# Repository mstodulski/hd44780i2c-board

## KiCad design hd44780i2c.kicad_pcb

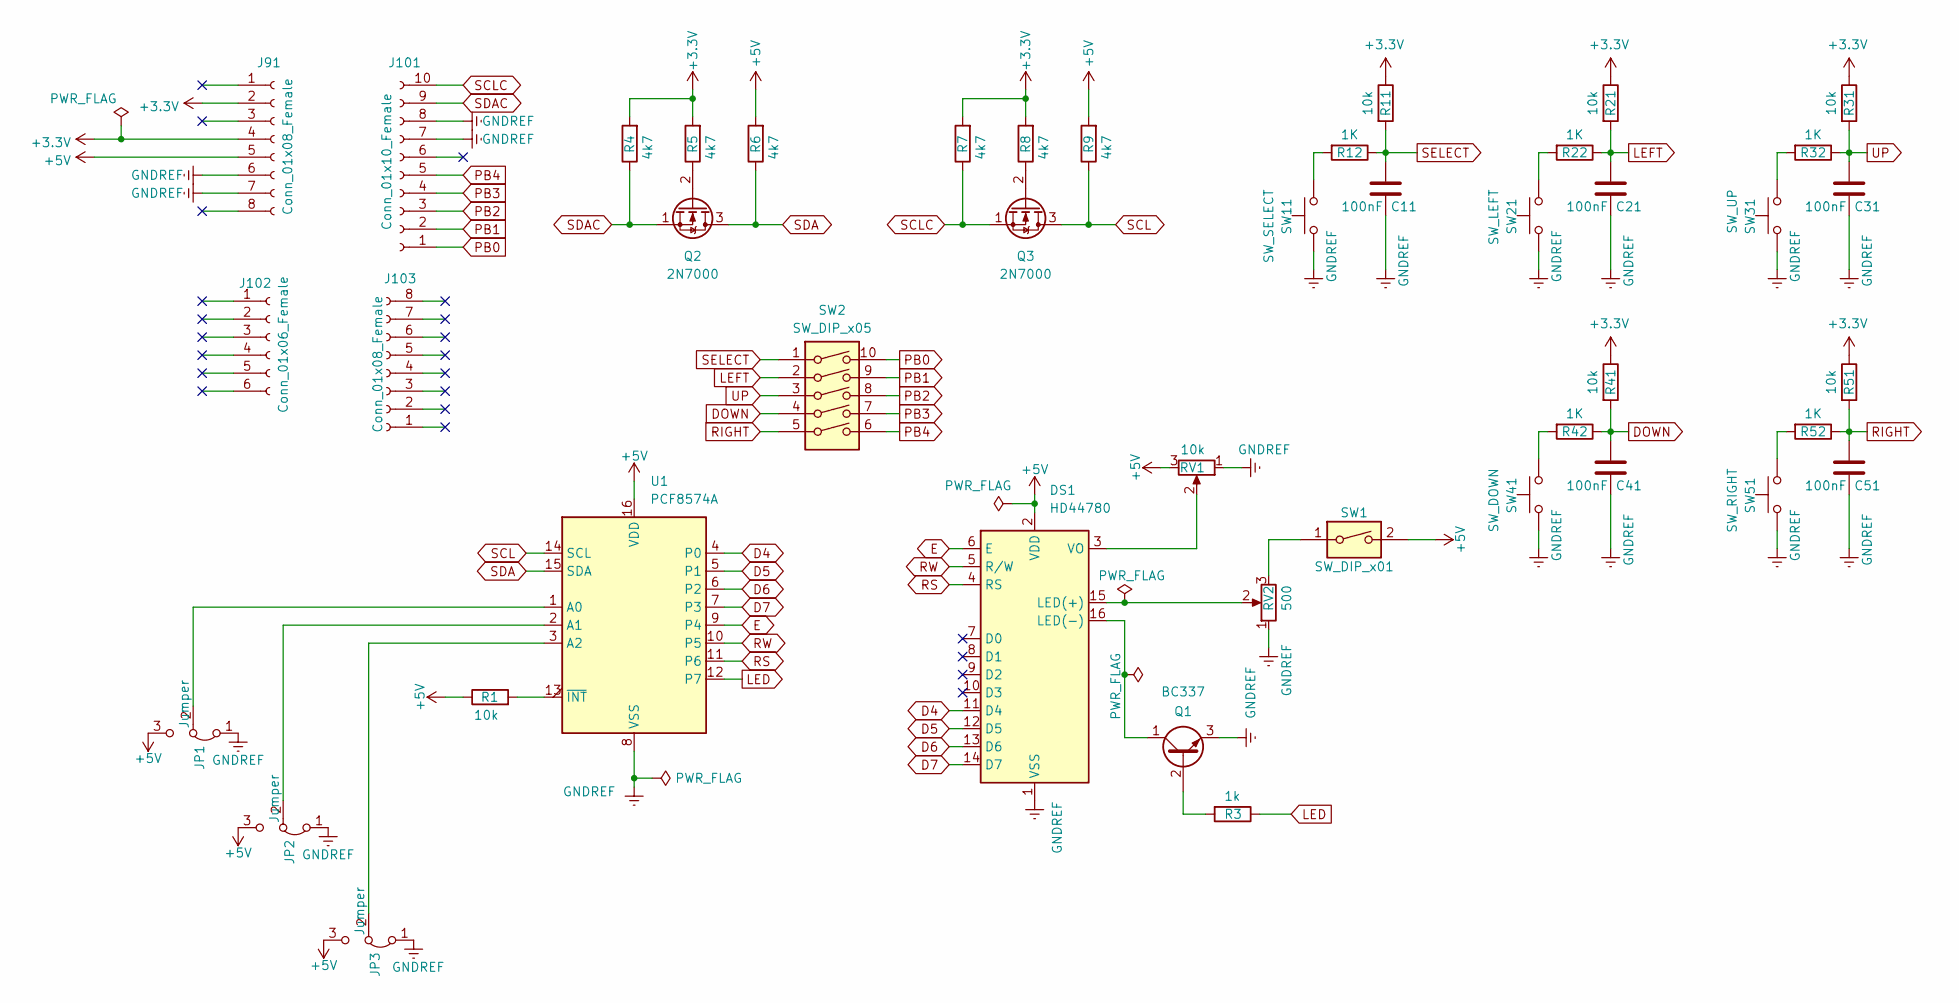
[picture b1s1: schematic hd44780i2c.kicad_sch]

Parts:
C11, C21, C31, C41, C51: 100nF; C_Disc_D5.0mm_W2.5mm_P2.50mm
DS1: HD44780; PinSocket_1x16_P2.54mm_Vertical
J91, J103: Conn_01x08_Female; PinSocket_1x08_P2.54mm_Vertical
J101: Conn_01x10_Female; PinSocket_1x10_P2.54mm_Vertical
J102: Conn_01x06_Female; PinSocket_1x06_P2.54mm_Vertical
JP1, JP2, JP3: Jumper; PinHeader_1x03_P2.54mm_Vertical
Q1: BC337; TO-92_Inline_Wide
Q2, Q3: 2N7000; TO-92_Inline_Wide
R1, R11, R21, R31, R41, R51: 10k; R_Axial_DIN0207_L6.3mm_D2.5mm_P10.16mm_Horizontal
R3: 1k; R_Axial_DIN0207_L6.3mm_D2.5mm_P10.16mm_Horizontal
R4, R5, R6, R7, R8, R9: 4k7; R_Axial_DIN0207_L6.3mm_D2.5mm_P10.16mm_Horizontal
R12, R22, R32, R42, R52: 1K; R_Axial_DIN0207_L6.3mm_D2.5mm_P10.16mm_Horizontal
RV1: 10k; Potentiometer_ACP_CA9-V5_Vertical
RV2: 500; Potentiometer_ACP_CA9-V5_Vertical
SW1: SW_DIP_x01; wlacznik katowy
SW2: SW_DIP_x05; DIP-10_W7.62mm
SW11: SW_SELECT; SW_PUSH_6mm_H4.3mm
SW21: SW_LEFT; SW_PUSH_6mm_H4.3mm
SW31: SW_UP; SW_PUSH_6mm_H4.3mm
SW41: SW_DOWN; SW_PUSH_6mm_H4.3mm
SW51: SW_RIGHT; SW_PUSH_6mm_H4.3mm
U1: PCF8574A; DIP-16_W7.62mm_Socket

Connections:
+3.3V: J91.2, J91.4, R4.2, R5.2, R7.2, R8.2, R11.1, R21.1, R31.1, R41.1, R51.1
+5V: DS1.2 (VDD), J91.5, JP1.3 (B), JP2.3 (B), JP3.3 (B), R1.1, R6.2, R9.2, RV1.3, SW1.2, U1.16 (VDD)
D4: DS1.11 (D4), U1.4 (P0)
D5: DS1.12 (D5), U1.5 (P1)
D6: DS1.13 (D6), U1.6 (P2)
D7: DS1.14 (D7), U1.7 (P3)
DOWN: C41.1, R41.2, R42.1, SW2.4
E: DS1.6 (E), U1.9 (P4)
GNDREF: C11.2, C21.2, C31.2, C41.2, C51.2, DS1.1 (VSS), J91.6, J91.7, J101.7, J101.8, JP1.1 (A), JP2.1 (A), JP3.1 (A), Q1.3 (E), RV1.1, RV2.1, SW11.1, SW21.1, SW31.1, SW41.1, SW51.1, U1.8 (VSS)
LED: R3.1, U1.12 (P7)
LEFT: C21.1, R21.2, R22.1, SW2.2
unnamed: DS1.15 (LED(+)), RV2.2
unnamed: DS1.16 (LED(-)), Q1.1 (C)
unnamed: DS1.3 (VO), RV1.2
unnamed: JP1.2 (C), U1.1 (A0)
unnamed: JP2.2 (C), U1.2 (A1)
unnamed: JP3.2 (C), U1.3 (A2)
unnamed: Q1.2 (B), R3.2
unnamed: Q2.2 (G), R5.1
unnamed: Q3.2 (G), R8.1
unnamed: R12.2, SW11.2
unnamed: R22.2, SW21.2
unnamed: R32.2, SW31.2
unnamed: R42.2, SW41.2
unnamed: R52.2, SW51.2
unnamed: RV2.3, SW1.1
unnamed: R1.2, U1.13 (~INT)
PB0: J101.1, SW2.10
PB1: J101.2, SW2.9
PB2: J101.3, SW2.8
PB3: J101.4, SW2.7
PB4: J101.5, SW2.6
RIGHT: C51.1, R51.2, R52.1, SW2.5
RS: DS1.4 (RS), U1.11 (P6)
RW: DS1.5 (R/W), U1.10 (P5)
SCL: Q3.3 (D), R9.1, U1.14 (SCL)
SCLC: J101.10, Q3.1 (S), R7.1
SDA: Q2.3 (D), R6.1, U1.15 (SDA)
SDAC: J101.9, Q2.1 (S), R4.1
SELECT: C11.1, R11.2, R12.1, SW2.1
UP: C31.1, R31.2, R32.1, SW2.3

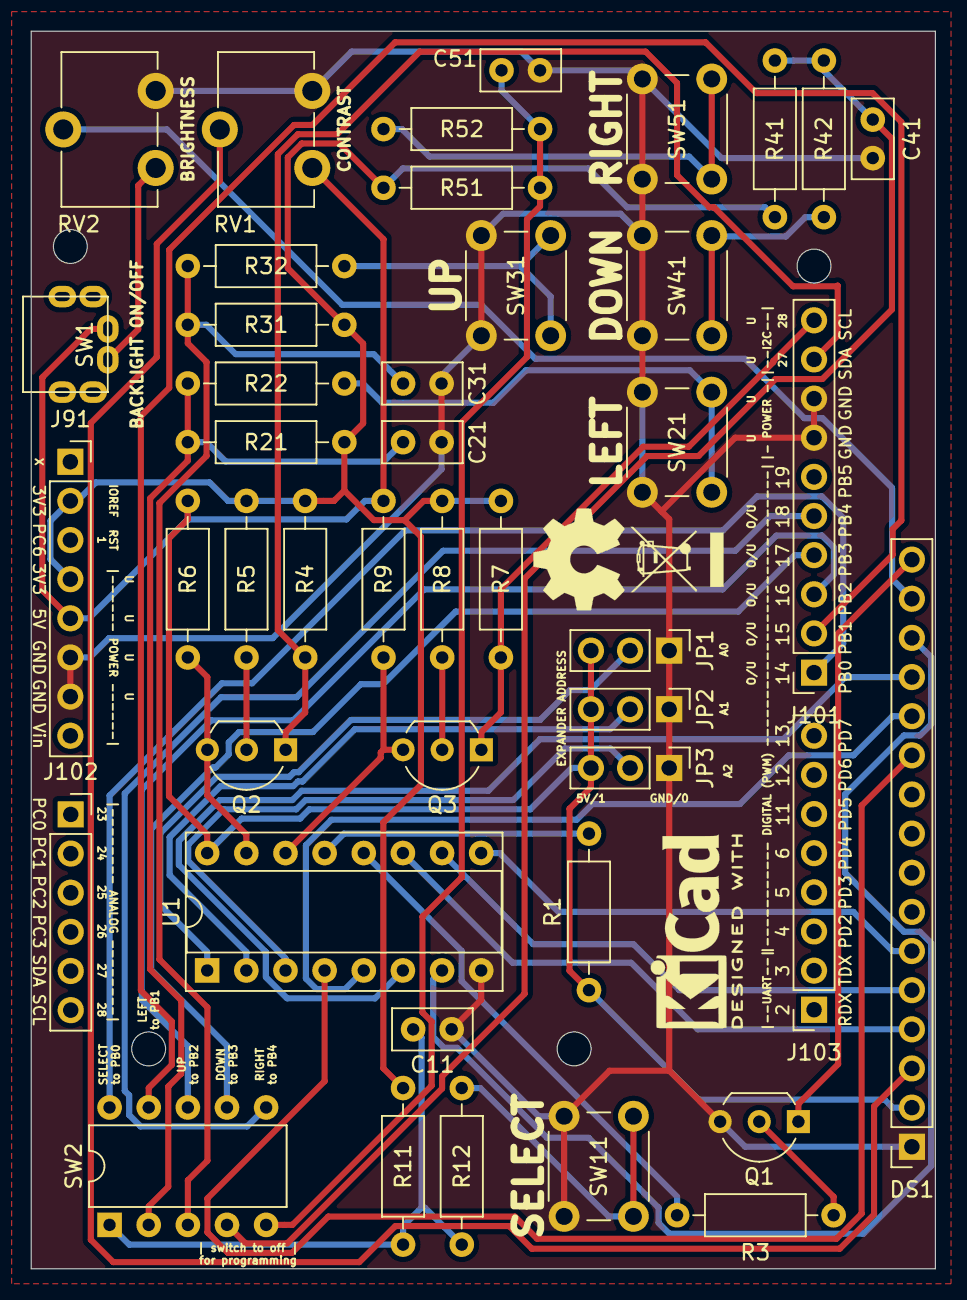
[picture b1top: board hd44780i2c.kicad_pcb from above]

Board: 2 copper layers, 58.7 x 80.3 mm, 47 parts (0 on the bottom side), 41 nets.

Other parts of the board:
REFL1: KiCad-Logo2_5mm_SilkScreen
REFL2: OSHW-Symbol_6.7x6mm_SilkScreen
REFL3: WEEE-Logo_4.2x6mm_SilkScreen

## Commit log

2024-04-19 modifications
